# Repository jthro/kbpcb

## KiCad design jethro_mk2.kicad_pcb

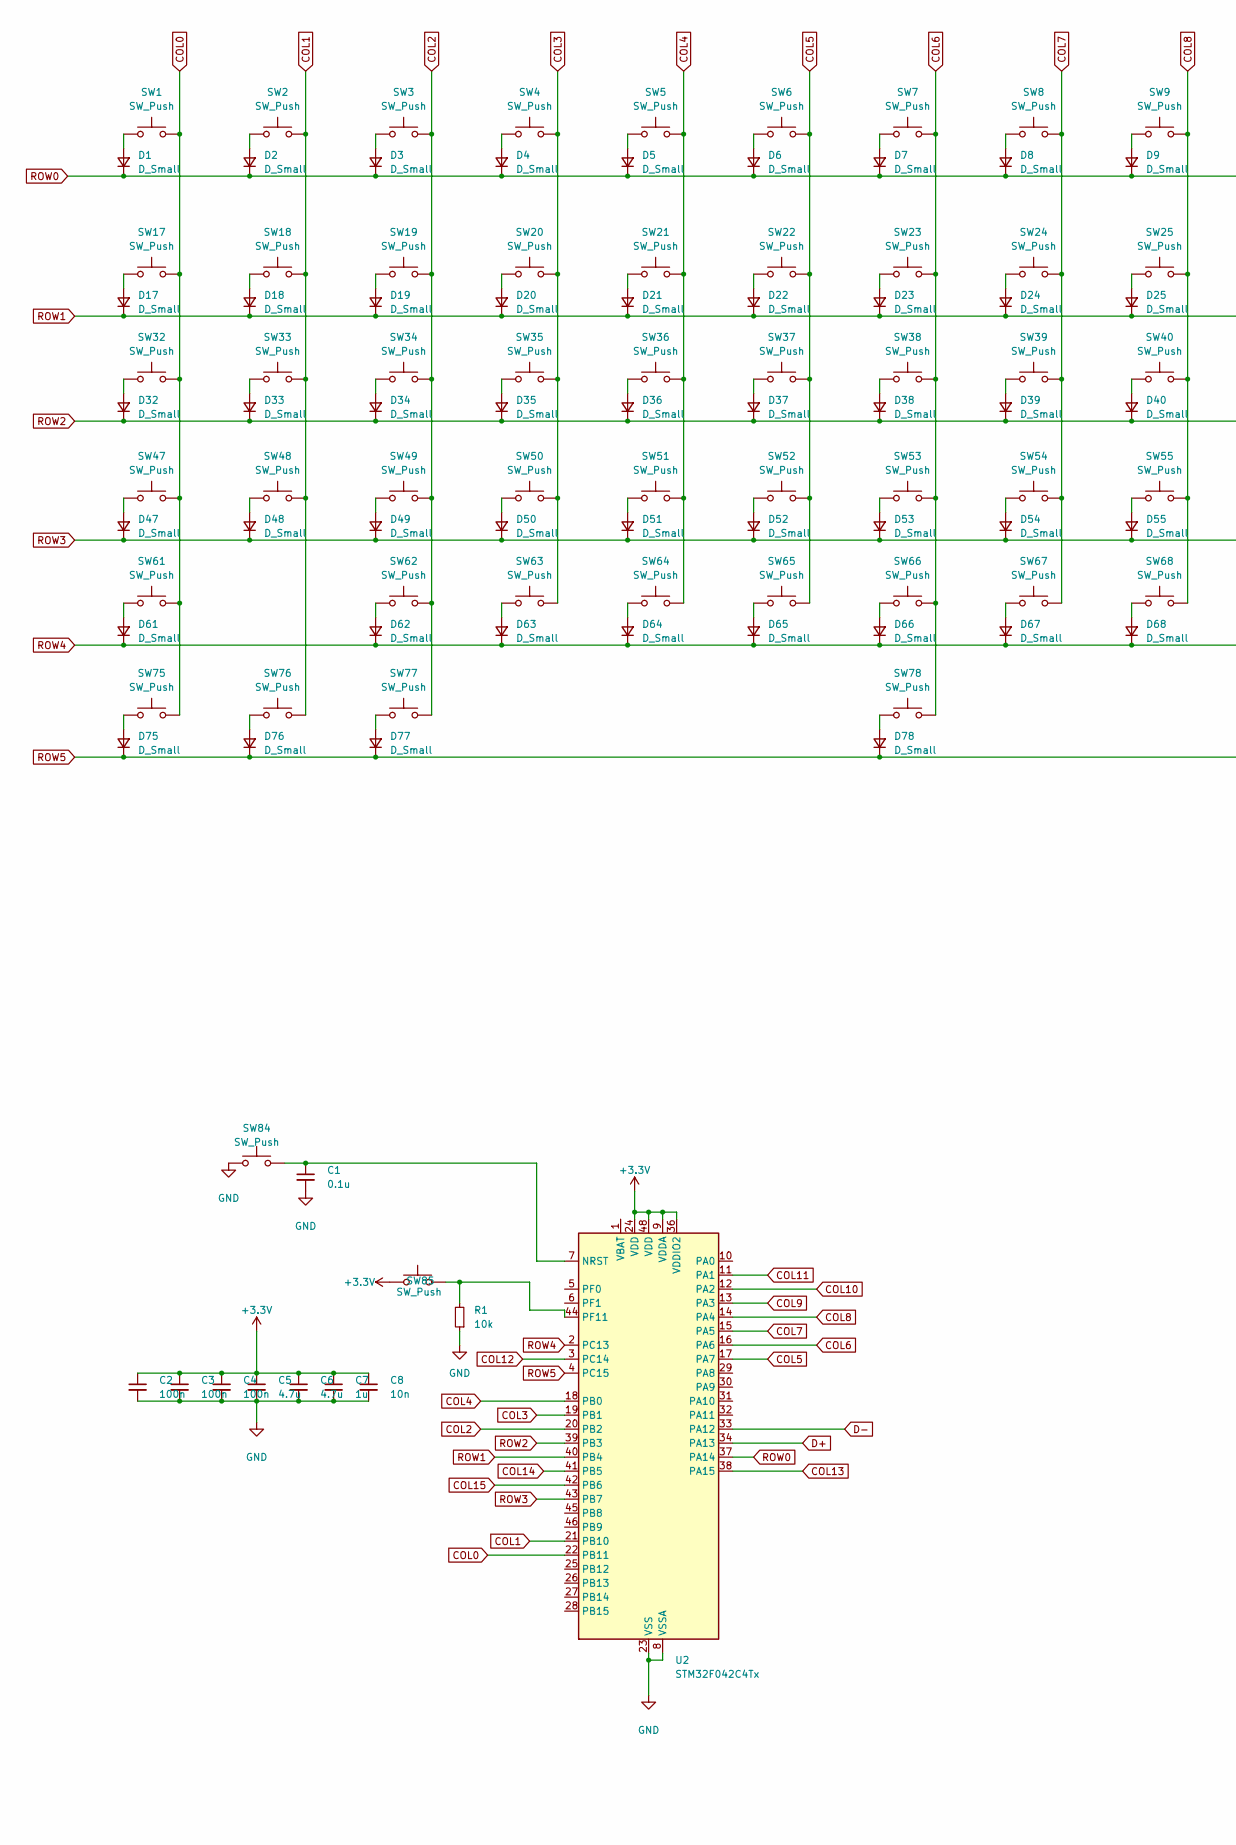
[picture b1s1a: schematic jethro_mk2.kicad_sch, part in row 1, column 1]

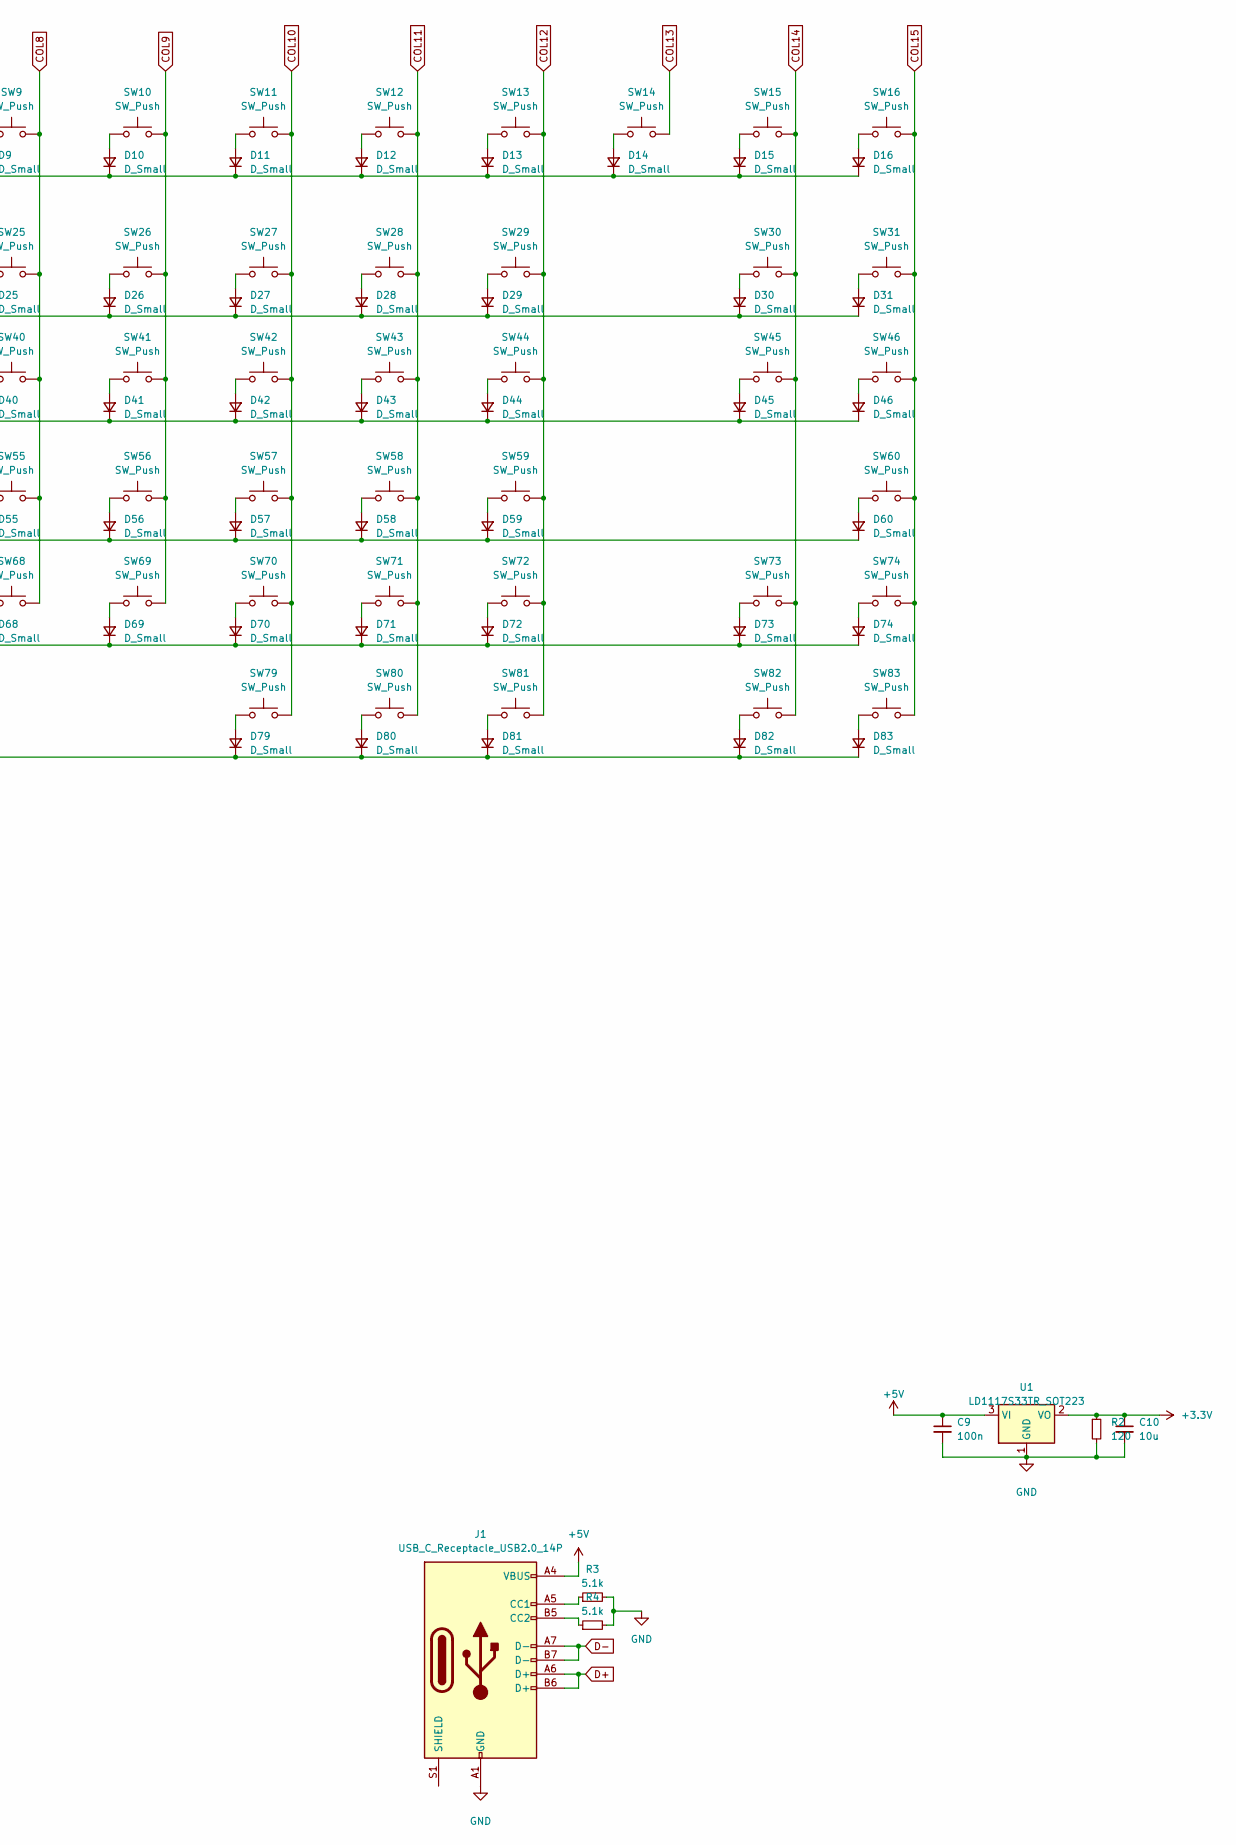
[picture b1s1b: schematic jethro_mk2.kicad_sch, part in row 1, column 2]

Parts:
C1: 0.1u; C_0805_2012Metric
C2, C3, C4, C9: 100n; C_0805_2012Metric
C5, C6: 4.7u; C_0805_2012Metric
C7: 1u; C_0805_2012Metric
C8: 10n; C_0805_2012Metric
C10: 10u; C_0805_2012Metric
D1, D2, D3, D4, D5, D6, D7, D8, D9, D10, D11, D12, D13, D14, D15, D16, D17, D18, D19, D20, D21, D22, D23, D24, D25, D26, D27, D28, D29, D30, D31, D32, D33, D34, D35, D36, D37, D38, D39, D40, D41, D42, D43, D44, D45, D46, D47, D48, D49, D50, D51, D52, D53, D54, D55, D56, D57, D58, D59, D60, D61, D62, D63, D64, D65, D66, D67, D68, D69, D70, D71, D72, D73, D74, D75, D76, D77, D78, D79, D80, D81, D82, D83: D_Small; D_DO-35_SOD27_P3.81mm_Vertical_AnodeUp
J1: USB_C_Receptacle_USB2.0_14P; USB_C_Receptacle_JAE_DX07S016JA1R1500
R1: 10k; R_0805_2012Metric
R2: 120; R_0805_2012Metric
R3, R4: 5.1k; R_0805_2012Metric
SW1, SW2, SW3, SW4, SW5, SW6, SW7, SW8, SW9, SW10, SW11, SW12, SW13, SW14, SW15, SW16, SW17, SW18, SW19, SW20, SW21, SW22, SW23, SW24, SW25, SW26, SW27, SW28, SW29, SW30, SW31, SW32, SW33, SW34, SW35, SW36, SW37, SW38, SW39, SW40, SW41, SW42, SW43, SW44, SW45, SW46, SW47, SW48, SW49, SW50, SW51, SW52, SW53, SW54, SW55, SW56, SW57, SW58, SW59, SW60, SW61, SW62, SW63, SW64, SW65, SW66, SW67, SW68, SW69, SW70, SW71, SW72, SW73, SW74, SW75, SW76, SW77, SW78, SW79, SW80, SW81, SW82, SW83: SW_Push; SW_Cherry_MX_PCB
SW84, SW85: SW_Push; SW_Push_1P1T_NO_CK_KSC6xxJ
U1: LD1117S33TR_SOT223; SOT-223-3_TabPin2
U2: STM32F042C4Tx; LQFP-48_7x7mm_P0.5mm

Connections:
+3.3V: C2.1, C3.1, C4.1, C5.1, C6.1, C7.1, C8.1, C10.1, R2.1, SW85.1, U1.2 (VO), U2.9 (VDDA), U2.24 (VDD), U2.36 (VDDIO2), U2.48 (VDD)
+5V: C9.1, J1.A4 (VBUS), J1.A9 (VBUS), J1.B4 (VBUS), J1.B9 (VBUS), U1.3 (VI)
COL0: SW1.2, SW17.2, SW32.2, SW47.2, SW61.2, SW75.2, U2.22 (PB11)
COL1: SW2.2, SW18.2, SW33.2, SW48.2, SW76.2, U2.21 (PB10)
COL2: SW3.2, SW19.2, SW34.2, SW49.2, SW62.2, SW77.2, U2.20 (PB2)
COL3: SW4.2, SW20.2, SW35.2, SW50.2, SW63.2, U2.19 (PB1)
COL4: SW5.2, SW21.2, SW36.2, SW51.2, SW64.2, U2.18 (PB0)
COL5: SW6.2, SW22.2, SW37.2, SW52.2, SW65.2, U2.17 (PA7)
COL6: SW7.2, SW23.2, SW38.2, SW53.2, SW66.2, SW78.2, U2.16 (PA6)
COL7: SW8.2, SW24.2, SW39.2, SW54.2, SW67.2, U2.15 (PA5)
COL8: SW9.2, SW25.2, SW40.2, SW55.2, SW68.2, U2.14 (PA4)
COL9: SW10.2, SW26.2, SW41.2, SW56.2, SW69.2, U2.13 (PA3)
COL10: SW11.2, SW27.2, SW42.2, SW57.2, SW70.2, SW79.2, U2.12 (PA2)
COL11: SW12.2, SW28.2, SW43.2, SW58.2, SW71.2, SW80.2, U2.11 (PA1)
COL12: SW13.2, SW29.2, SW44.2, SW59.2, SW72.2, SW81.2, U2.3 (PC14)
COL13: SW14.2, U2.38 (PA15)
COL14: SW15.2, SW30.2, SW45.2, SW73.2, SW82.2, U2.41 (PB5)
COL15: SW16.2, SW31.2, SW46.2, SW60.2, SW74.2, SW83.2, U2.42 (PB6)
D+: J1.A6 (D+), J1.B6 (D+), U2.34 (PA13)
D-: J1.A7 (D-), J1.B7 (D-), U2.33 (PA12)
GND: C1.2, C2.2, C3.2, C4.2, C5.2, C6.2, C7.2, C8.2, C9.2, C10.2, J1.A1 (GND), J1.A12 (GND), J1.B1 (GND), J1.B12 (GND), R1.1, R2.2, R3.2, R4.2, SW84.1, U1.1 (GND), U2.8 (VSSA), U2.23 (VSS), U2.35 (VSS), U2.47 (VSS)
unnamed: D1.2 (A), SW1.1
unnamed: D2.2 (A), SW2.1
unnamed: D3.2 (A), SW3.1
unnamed: D4.2 (A), SW4.1
unnamed: D5.2 (A), SW5.1
unnamed: D6.2 (A), SW6.1
unnamed: D7.2 (A), SW7.1
unnamed: D8.2 (A), SW8.1
unnamed: D9.2 (A), SW9.1
unnamed: D10.2 (A), SW10.1
unnamed: D11.2 (A), SW11.1
unnamed: D12.2 (A), SW12.1
unnamed: D13.2 (A), SW13.1
unnamed: D14.2 (A), SW14.1
unnamed: D15.2 (A), SW15.1
unnamed: D16.2 (A), SW16.1
unnamed: D17.2 (A), SW17.1
unnamed: D18.2 (A), SW18.1
unnamed: D19.2 (A), SW19.1
unnamed: D20.2 (A), SW20.1
unnamed: D21.2 (A), SW21.1
unnamed: D22.2 (A), SW22.1
unnamed: D23.2 (A), SW23.1
unnamed: D24.2 (A), SW24.1
unnamed: D25.2 (A), SW25.1
unnamed: D26.2 (A), SW26.1
unnamed: D27.2 (A), SW27.1
unnamed: D28.2 (A), SW28.1
unnamed: D29.2 (A), SW29.1
unnamed: D30.2 (A), SW30.1
unnamed: D31.2 (A), SW31.1
unnamed: D32.2 (A), SW32.1
unnamed: D33.2 (A), SW33.1
unnamed: D34.2 (A), SW34.1
unnamed: D35.2 (A), SW35.1
unnamed: D36.2 (A), SW36.1
unnamed: D37.2 (A), SW37.1
unnamed: D38.2 (A), SW38.1
unnamed: D39.2 (A), SW39.1
unnamed: D40.2 (A), SW40.1
unnamed: D41.2 (A), SW41.1
unnamed: D42.2 (A), SW42.1
unnamed: D43.2 (A), SW43.1
unnamed: D44.2 (A), SW44.1
unnamed: D45.2 (A), SW45.1
unnamed: D46.2 (A), SW46.1
unnamed: D47.2 (A), SW47.1
unnamed: D48.2 (A), SW48.1
unnamed: D49.2 (A), SW49.1
unnamed: D50.2 (A), SW50.1
unnamed: D51.2 (A), SW51.1
unnamed: D52.2 (A), SW52.1
unnamed: D53.2 (A), SW53.1
unnamed: D54.2 (A), SW54.1
unnamed: D55.2 (A), SW55.1
unnamed: D56.2 (A), SW56.1
unnamed: D57.2 (A), SW57.1
unnamed: D58.2 (A), SW58.1
unnamed: D59.2 (A), SW59.1
unnamed: D60.2 (A), SW60.1
unnamed: D61.2 (A), SW61.1
unnamed: D62.2 (A), SW62.1
unnamed: D63.2 (A), SW63.1
unnamed: D64.2 (A), SW64.1
unnamed: D65.2 (A), SW65.1
unnamed: D66.2 (A), SW66.1
unnamed: D67.2 (A), SW67.1
unnamed: D68.2 (A), SW68.1
unnamed: D69.2 (A), SW69.1
unnamed: D70.2 (A), SW70.1
unnamed: D71.2 (A), SW71.1
unnamed: D72.2 (A), SW72.1
unnamed: D73.2 (A), SW73.1
unnamed: D74.2 (A), SW74.1
unnamed: D75.2 (A), SW75.1
unnamed: D76.2 (A), SW76.1
unnamed: D77.2 (A), SW77.1
unnamed: D78.2 (A), SW78.1
unnamed: D79.2 (A), SW79.1
unnamed: D80.2 (A), SW80.1
unnamed: D81.2 (A), SW81.1
unnamed: D82.2 (A), SW82.1
unnamed: D83.2 (A), SW83.1
unnamed: J1.A5 (CC1), R3.1
unnamed: J1.B5 (CC2), R4.1
unnamed: C1.1, SW84.2, U2.7 (NRST)
unnamed: R1.2, SW85.2, U2.44 (PF11)
ROW0: D1.1 (K), D2.1 (K), D3.1 (K), D4.1 (K), D5.1 (K), D6.1 (K), D7.1 (K), D8.1 (K), D9.1 (K), D10.1 (K), D11.1 (K), D12.1 (K), D13.1 (K), D14.1 (K), D15.1 (K), D16.1 (K), U2.37 (PA14)
ROW1: D17.1 (K), D18.1 (K), D19.1 (K), D20.1 (K), D21.1 (K), D22.1 (K), D23.1 (K), D24.1 (K), D25.1 (K), D26.1 (K), D27.1 (K), D28.1 (K), D29.1 (K), D30.1 (K), D31.1 (K), U2.40 (PB4)
ROW2: D32.1 (K), D33.1 (K), D34.1 (K), D35.1 (K), D36.1 (K), D37.1 (K), D38.1 (K), D39.1 (K), D40.1 (K), D41.1 (K), D42.1 (K), D43.1 (K), D44.1 (K), D45.1 (K), D46.1 (K), U2.39 (PB3)
ROW3: D47.1 (K), D48.1 (K), D49.1 (K), D50.1 (K), D51.1 (K), D52.1 (K), D53.1 (K), D54.1 (K), D55.1 (K), D56.1 (K), D57.1 (K), D58.1 (K), D59.1 (K), D60.1 (K), U2.43 (PB7)
ROW4: D61.1 (K), D62.1 (K), D63.1 (K), D64.1 (K), D65.1 (K), D66.1 (K), D67.1 (K), D68.1 (K), D69.1 (K), D70.1 (K), D71.1 (K), D72.1 (K), D73.1 (K), D74.1 (K), U2.2 (PC13)
ROW5: D75.1 (K), D76.1 (K), D77.1 (K), D78.1 (K), D79.1 (K), D80.1 (K), D81.1 (K), D82.1 (K), D83.1 (K), U2.4 (PC15)

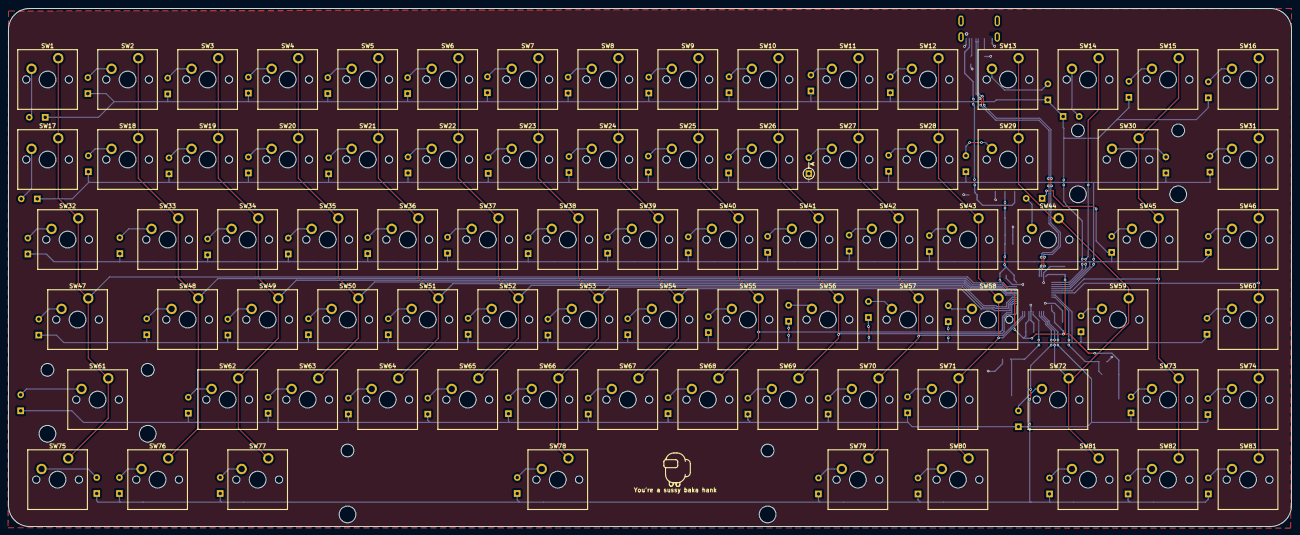
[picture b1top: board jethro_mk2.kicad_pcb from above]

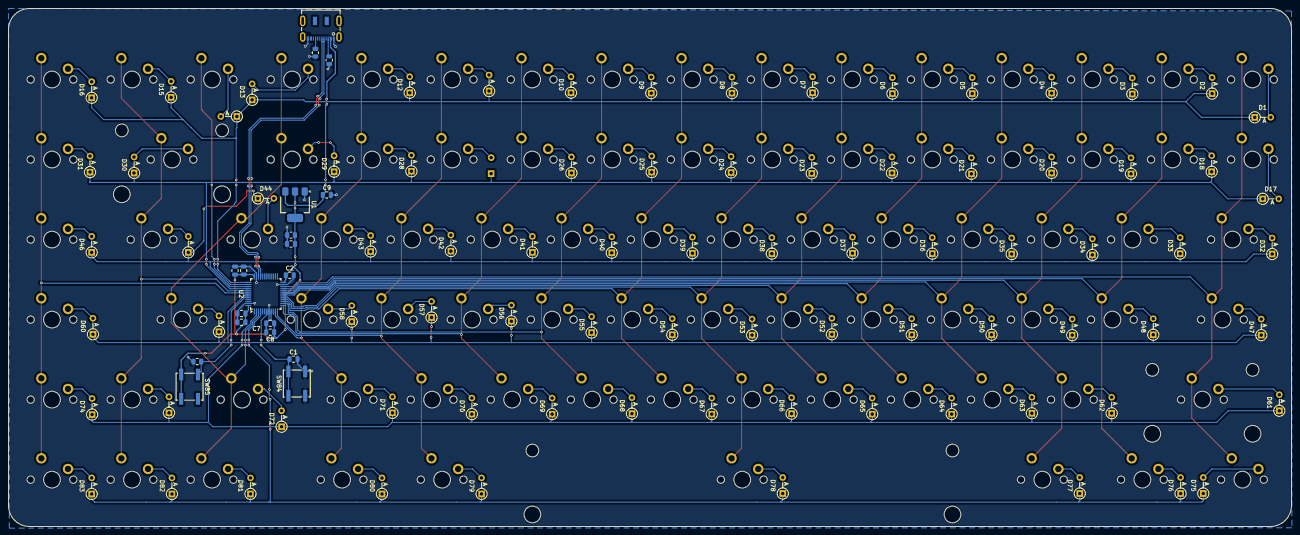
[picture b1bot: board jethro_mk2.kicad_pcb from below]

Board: 2 copper layers, 305.4 x 123.3 mm, 185 parts (101 on the bottom side), 114 nets.

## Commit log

2025-01-27 add dependencies as submodules
2025-01-29 first iteration done
2025-01-29 remove accidental proprietary model
2025-04-24 Second revision complete
